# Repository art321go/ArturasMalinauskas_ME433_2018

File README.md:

# ArturasMalinauskas_ME433_2018

Arturas Malinauskas
4/9/2018

This repository contains assignments completed to practice various aspects of high level mechatronics

This line is testing commit changes

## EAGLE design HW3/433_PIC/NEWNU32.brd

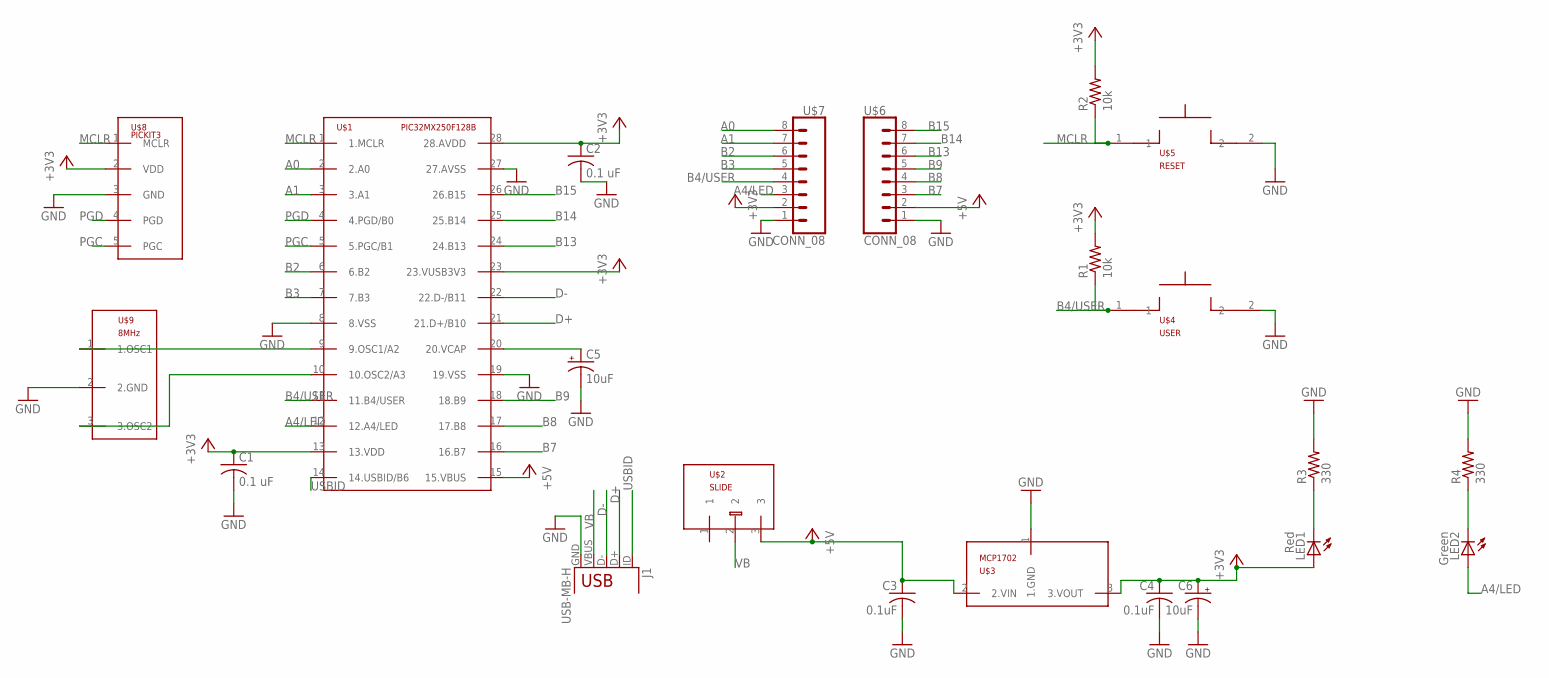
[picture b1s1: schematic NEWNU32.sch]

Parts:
C1, C2: 0.1 uF; C025-025X050
C3, C4: 0.1uF; C025-025X050
C5, C6: 10uF; B45181B
J1: USB-MB-H
LED1: Red; LED3MM
LED2: Green; LED3MM
R1, R2: 10k; 0207/10
R3, R4: 330; 0207/10
U$1: PIC32MX250F128B; DIL28-3
U$2: SLIDE
U$3: MCP1702; TO92
U$4: USER; PB
U$5: RESET; PB
U$6, U$7: CONN_08; 1X08
U$8: PICKIT3; 1X05
U$9: 8MHz; OSC

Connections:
+3V3: C1.1, C2.1, C4.1, C6.+, LED1.A, R1.2, R2.2, U$1.13 (13.VDD), U$1.23 (23.VUSB3V3), U$1.28 (28.AVDD), U$3.3 (3.VOUT), U$7.2, U$8.2 (VDD)
+5V: C3.1, U$1.15 (15.VBUS), U$2.3, U$3.2 (2.VIN), U$6.2
A0: U$1.2 (2.A0), U$7.8
A1: U$1.3 (3.A1), U$7.7
A4/LED: LED2.A, U$1.12 (12.A4/LED), U$7.3
B2: U$1.6 (6.B2), U$7.6
B3: U$1.7 (7.B3), U$7.5
B4/USER: R1.1, U$1.11 (11.B4/USER), U$4.1, U$7.4
B7: U$1.16 (16.B7), U$6.3
B8: U$1.17 (17.B8), U$6.4
B9: U$1.18 (18.B9), U$6.5
B13: U$1.24 (24.B13), U$6.6
B14: U$1.25 (25.B14), U$6.7
B15: U$1.26 (26.B15), U$6.8
D+: J1.D+, U$1.21 (21.D+/B10)
D-: J1.D-, U$1.22 (22.D-/B11)
GND: C1.2, C2.2, C3.2, C4.2, C5.-, C6.-, J1.GND, R3.2, R4.2, U$1.8 (8.VSS), U$1.19 (19.VSS), U$1.27 (27.AVSS), U$3.1 (1.GND), U$4.2, U$5.2, U$6.1, U$7.1, U$8.3 (GND), U$9.2 (2.GND)
MCLR: R2.1, U$1.1 (1.MCLR), U$5.1, U$8.1 (MCLR)
unnamed: LED2.K (C), R4.1
unnamed: LED1.K (C), R3.1
unnamed: U$1.9 (9.OSC1/A2), U$9.1 (1.OSC1)
unnamed: U$1.10 (10.OSC2/A3), U$9.3 (3.OSC2)
unnamed: C5.+, U$1.20 (20.VCAP)
PGC: U$1.5 (5.PGC/B1), U$8.5 (PGC)
PGD: U$1.4 (4.PGD/B0), U$8.4 (PGD)
USBID: J1.ID, U$1.14 (14.USBID/B6)
VB: J1.VBUS, U$2.2

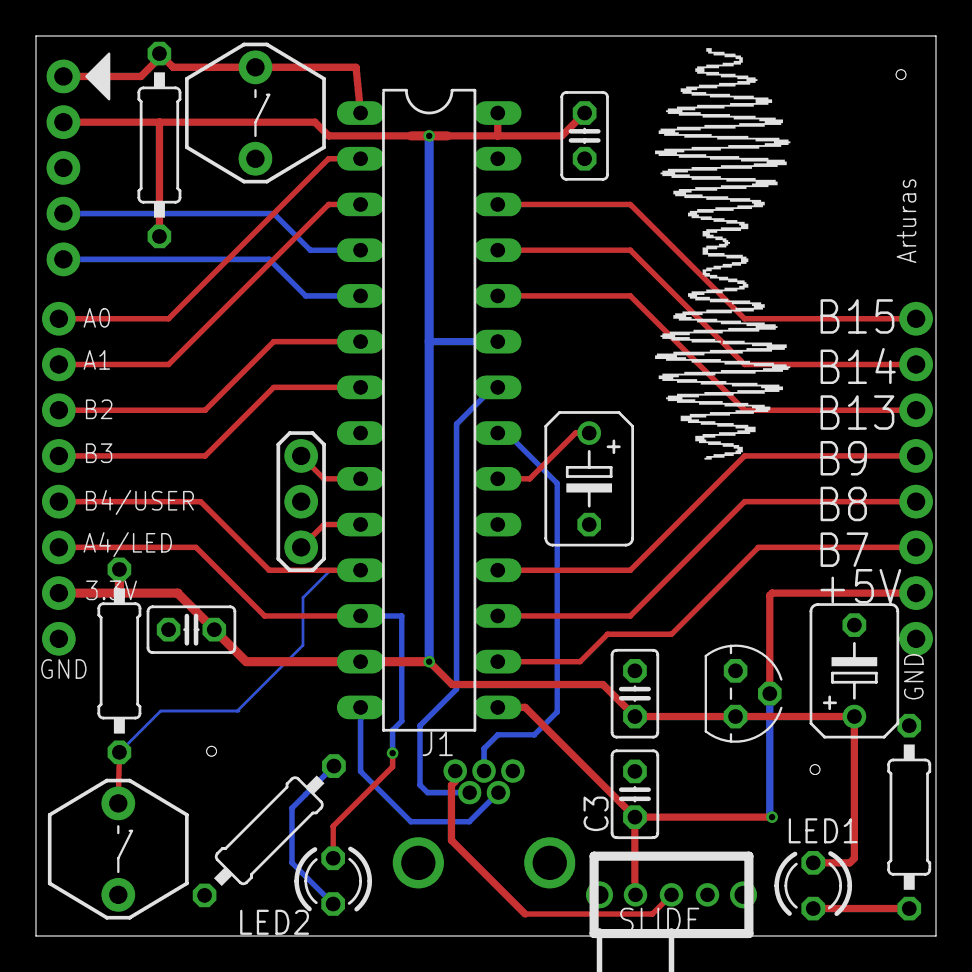
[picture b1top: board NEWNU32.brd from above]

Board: 2 copper layers, 50.0 x 50.0 mm, 22 parts (0 on the bottom side), 27 nets.

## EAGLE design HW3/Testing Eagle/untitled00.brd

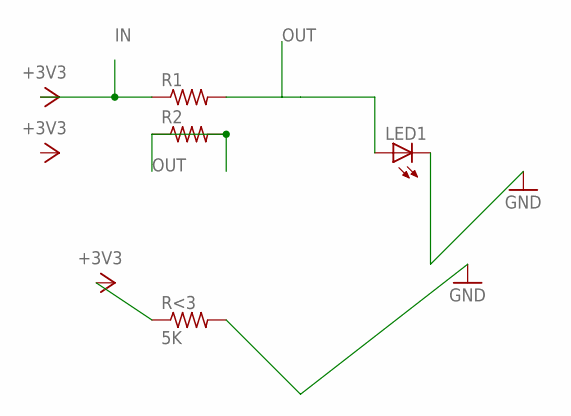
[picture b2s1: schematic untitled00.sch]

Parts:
LED1: LED3MM
R1, R2: R-US_0207/7; 0207/7
R<3: 5K; 0207/7

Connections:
+3V3: R<3.1
GND: LED1.K (C), R<3.2
IN: R1.1
OUT: LED1.A, R1.2, R2.1, R2.2

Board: 2 copper layers, 4 parts (0 on the bottom side), 2 nets, no tracks yet.

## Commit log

2018-04-09 Commit No.1
    Basic Description for the Repository was created
2018-04-09 Test
    Testing Commits
2018-04-10 Added Git ignore
2018-04-10 Added PIC circuit to newly made HW1 folder
2018-04-10 Initial testing and learning with EAGLE
2018-04-12 Initial population of library for the NEWNU32
2018-04-16 Starting work on creating a New NU32 PCB for HW2
    Populated Library, created a schematic, and started a board file in Eagle
2018-04-17 Finished Initial Board
2018-04-17 Added ZIp to surface folder
2018-04-21 Built HW1 Circuit and Began Code
2018-04-21 Created main.c for HW1
2018-04-21 Setting PRAGMA Values
2018-04-23 Finished HW1 (better late than never i suppose)
2018-04-29 FIxed HW1, PIC Button Bounce
2018-04-29 Cleaned up directory
2018-05-03 SPI work
2018-05-03 Implemented HW1 with Harmony for HW8
2018-05-04 HW9 and HW4 progress
2018-05-04 Finished HW4
2018-05-15 Progress on various homework assignments
2018-05-15 Writing HW5 functions for reading/writing i2c
2018-05-17 Created HelloWorld for andriod
2018-05-19 Finished HW5 and progress on HW13
2018-05-19 added HW5 and 12 demo videos to their respective folders
2018-05-19 Created Schematic for HW6
2018-05-19 Progress on HW6
2018-05-20 Finished HW6
2018-05-21 Schematic for HW7
2018-05-21 Schematic for the IMU
2018-05-21 Allowing LCD debugging for IMU
2018-05-22 work on HW7 and 13
2018-05-24 struggled but finally got WHO_AM_I for the IMU to read
    <<<<<<<<< :(
2018-05-26 IMU progress
2018-05-26 Reading from IMU and drawing a crosshair on the LCD
2018-05-27 HW7 working except some crosshair funkiness
2018-05-27 HW7 minor edit
2018-05-27 HW7 fully working
2018-05-28 Added demo vid for HW7
2018-05-28 HW8 with IMU code now working
2018-05-29 HW9 issues
2018-05-29 Finished HW9
2018-05-31 Starting HW11
2018-06-01 Finished HW 11
2018-06-01 modifying hw9 for hw10
2018-06-01 HW10 MAF working
2018-06-01 Finished HW10
2018-06-04 Making HW14, finished 13
2018-06-05 Working on HW14
2018-06-05 HW14 progress
2018-06-05 Finished HW14
2018-06-16 Motor Control
2018-06-17 HW15images
2018-06-17 Adding Pictures
2018-06-17 Photo Updates
